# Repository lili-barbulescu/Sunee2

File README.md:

# Sunee
Wearable device for monitoring UV exposure

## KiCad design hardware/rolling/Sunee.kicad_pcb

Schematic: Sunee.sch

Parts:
BT1: Battery; 3034
SW1: Power; DPDT

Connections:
GND: BT1.2; also elsewhere on the board
unnamed: BT1.1, SW1.1
VCC: SW1.2; also elsewhere on the board

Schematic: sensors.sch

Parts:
ACC1: BMA253; BMA250E
C1, C3: 0.1uF; C_0402
C4: 100nF; C_0402
R1, R2, R5: 5K; R_0402
R6: 10K; R_0402
R14, R15: 100; R_0402
UV1: SI1133

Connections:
/BLE/INT_ACC1: ACC1.5; also elsewhere on the board
/BLE/INT_ACC2: ACC1.6; also elsewhere on the board
/BLE/INT_UV: R5.2, UV1.4; also elsewhere on the board
/BLE/SCL: R14.1; also elsewhere on the board
/BLE/SDA: R15.1; also elsewhere on the board
/sensors/SCL_UP: ACC1.12, R2.2, R14.2, UV1.2
/sensors/SDA_UP: ACC1.2, R1.2, R15.2, UV1.1
GND: ACC1.1, ACC1.4, ACC1.8, ACC1.9, C1.2, C3.2, C4.2, UV1.8; also elsewhere on the board
unnamed: R6.1, UV1.6, UV1.7, UV1.9
VCC: ACC1.3, ACC1.7, ACC1.11, C1.1, C3.1, C4.1, R1.1, R2.1, R5.1, R6.2, UV1.3; also elsewhere on the board

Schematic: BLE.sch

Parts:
1.0uF1: C_Small; C_0402
10uH1: L_Small; R_0603
15nH1: L_Small; R_0402
C5, C6: 12pF; C_0402
C7: 0.1uF; C_0402
MDBT42V_1: MDBT42V
P1: CONN_01X04; Socket_Strip_Straight_1x04
Y1: 32.768 kHz; K135

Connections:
/BLE/BUZZER: MDBT42V_1.24; also elsewhere on the board
/BLE/INT_ACC1: MDBT42V_1.12; also elsewhere on the board
/BLE/INT_ACC2: MDBT42V_1.11; also elsewhere on the board
/BLE/INT_UV: MDBT42V_1.19; also elsewhere on the board
/BLE/LED4: MDBT42V_1.7; also elsewhere on the board
/BLE/LED5: MDBT42V_1.6; also elsewhere on the board
/BLE/LED6: MDBT42V_1.5; also elsewhere on the board
/BLE/SCL: MDBT42V_1.8; also elsewhere on the board
/BLE/SDA: MDBT42V_1.9; also elsewhere on the board
GND: 1.0uF1.2, C5.2, C6.2, C7.2, MDBT42V_1.1, MDBT42V_1.10, MDBT42V_1.18, MDBT42V_1.29, P1.1; also elsewhere on the board
unnamed: 1.0uF1.1, 15nH1.2, MDBT42V_1.21
unnamed: 10uH1.1, MDBT42V_1.22
unnamed: 10uH1.2, 15nH1.1
unnamed: C5.1, MDBT42V_1.15, Y1.1
unnamed: C6.1, MDBT42V_1.16, Y1.2
unnamed: MDBT42V_1.2, P1.2
unnamed: MDBT42V_1.4, P1.3
VCC: C7.1, MDBT42V_1.20, MDBT42V_1.26, P1.4; also elsewhere on the board

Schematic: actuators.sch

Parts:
BZ1: BUZZER; PS1240P02
C8: 1uF; C_0402
D2: LED[4..6]; ASMB-MTB0-0A3A2
R7, R11, R12, R13: 330; R_0402

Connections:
/BLE/BUZZER: R7.1; also elsewhere on the board
/BLE/LED4: R11.1; also elsewhere on the board
/BLE/LED5: R12.1; also elsewhere on the board
/BLE/LED6: R13.1; also elsewhere on the board
GND: BZ1.2 (GND); also elsewhere on the board
unnamed: BZ1.1 (SIGN), C8.2
unnamed: C8.1, R7.2
unnamed: D2.2, R13.2
unnamed: D2.3, R12.2
unnamed: D2.4, R11.2
VCC: D2.1; also elsewhere on the board

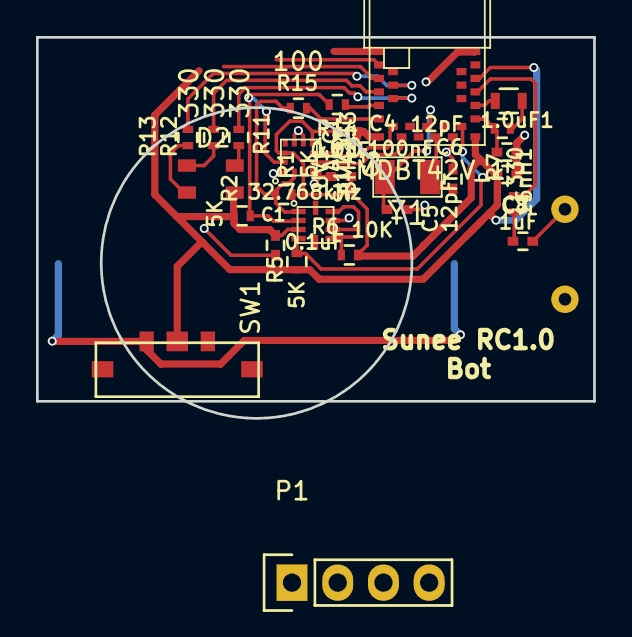
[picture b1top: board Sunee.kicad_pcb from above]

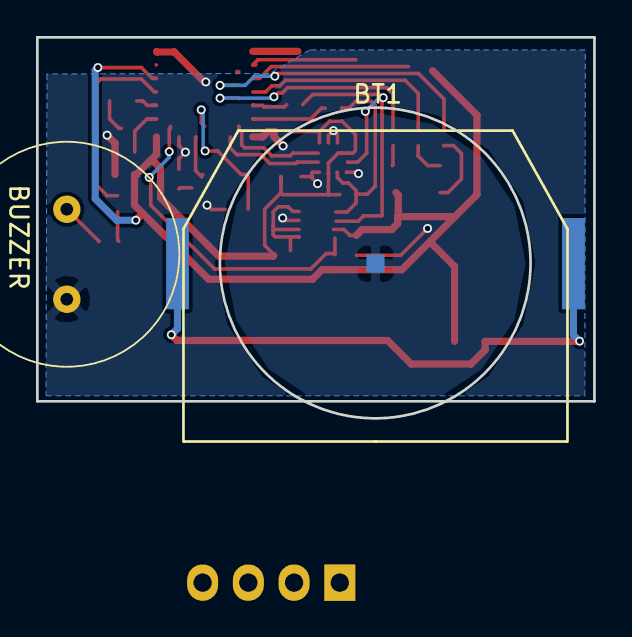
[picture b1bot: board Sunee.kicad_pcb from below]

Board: 2 copper layers, 30.9 x 21.2 mm, 29 parts (2 on the bottom side), 27 nets.

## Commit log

2017-08-26 Added several symbols
2017-08-28 test
2017-08-28 dogs
2017-08-28 Added several files
2017-08-28 modify 1
2017-08-28 added .gitignore
2017-08-28 just a test
2017-08-28 Added root sheet, BLE, sensors
2017-08-30 Sensors
2017-08-30 BLE schematic
2017-08-30 fixes, inter-module interrupt lines
2017-08-30 Small change in BLE
2017-08-30 removed .bak files
2017-08-30 Added UART port
2017-09-01 Added footprints
2017-09-01 butoane
2017-09-06 Added netlist
2017-09-07 Fixes before layout
2017-09-07 ERC before layout
2017-09-07 headers for LEDS
2017-09-14 finished board layout
2017-10-01 Finished B1.0 layout
2017-10-06 Released B1
2017-11-17 Added flash script for nrf52 using STM32 Programmer
2017-11-17 Added Nordic nrf52 SDK; Added working blinky code
2017-11-17 Added nRF52-compatible version of openocd-0.10.0
2017-11-24 update OpenOCD
2017-11-24 updated flash scrips(generalized)
2017-12-04 Almost finished B2 HW
2017-12-29 Moving to 4 layer layout(not implemented yet)
2018-01-27 Added BLE example code.
2018-02-04 Ignoring binaries
